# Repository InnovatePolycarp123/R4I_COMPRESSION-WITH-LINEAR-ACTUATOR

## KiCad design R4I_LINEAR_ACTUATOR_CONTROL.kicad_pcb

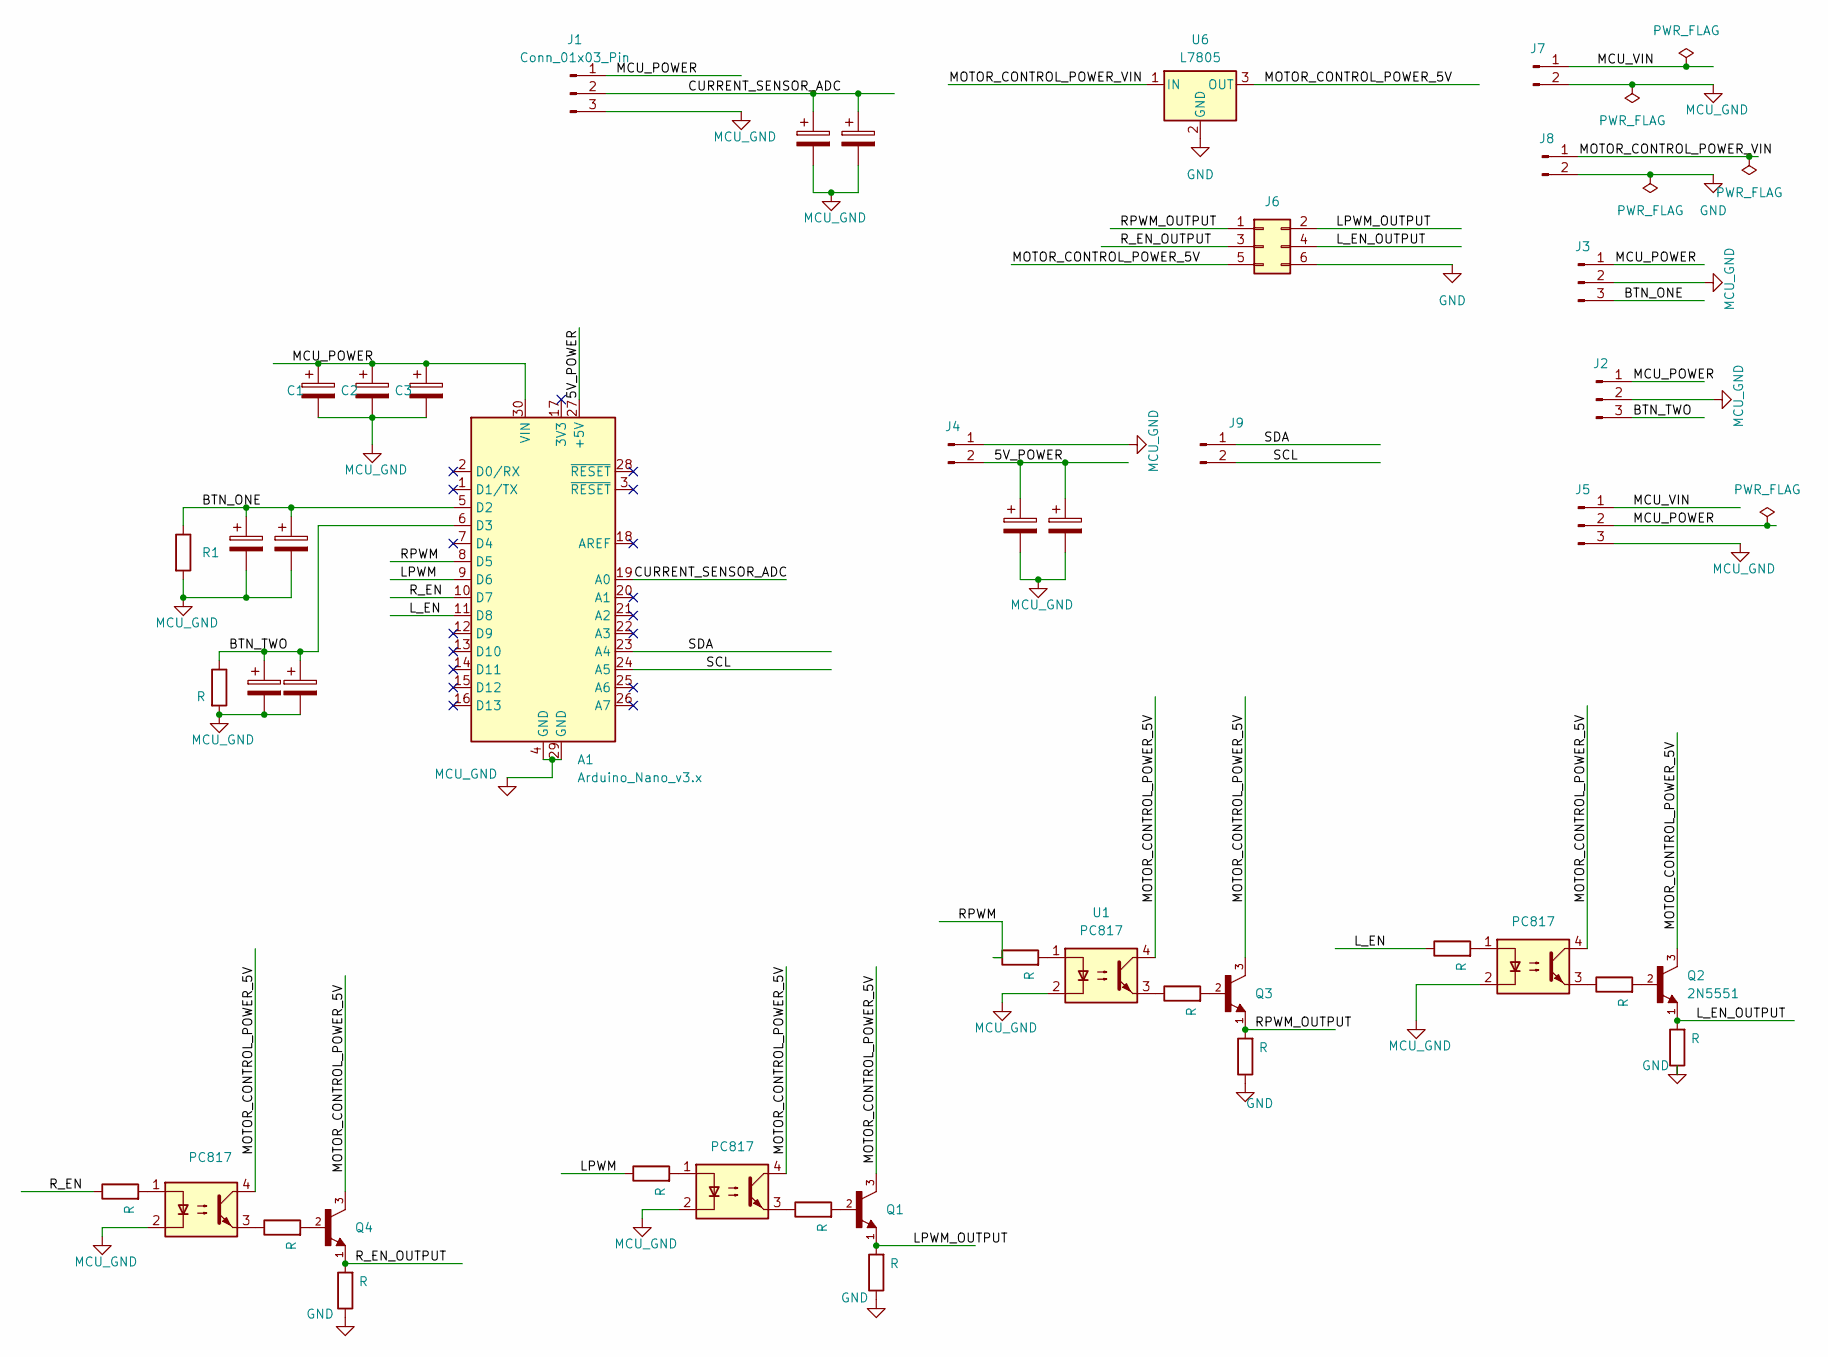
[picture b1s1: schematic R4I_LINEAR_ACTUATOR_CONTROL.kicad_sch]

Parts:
A1: Arduino_Nano_v3.x; Arduino_Nano
C1, C2, C3, C4, C5, C6, C7, C8, C9, C10, C11: C_Polarized; CP_Radial_D5.0mm_P2.50mm
J1, J2, J3, J5: Conn_01x03_Pin; JST_EH_B3B-EH-A_1x03_P2.50mm_Vertical
J4, J7, J8, J9: Conn_01x02_Pin; JST_EH_B2B-EH-A_1x02_P2.50mm_Vertical
J6: Conn_02x03_Row_Letter_Last; PinHeader_2x03_P2.54mm_Vertical
Q1, Q2, Q3, Q4: 2N5551; TO-92L_Wide; PARTREV 5
R1, R2, R3, R4, R5, R6, R7, R8, R9, R10, R11, R12, R13, R14: R; R_Axial_DIN0207_L6.3mm_D2.5mm_P7.62mm_Horizontal
U1, U2, U3, U4: PC817; DIP-4_W7.62mm
U6: L7805; TO-220-3_Vertical

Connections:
/5V_POWER: A1.27 (+5V), C10.1, C11.1, J4.2
/BTN_ONE: A1.5 (D2), C4.1, C5.1, J3.3, R1.1
/BTN_TWO: A1.6 (D3), C6.1, C7.1, J2.3, R2.1
/CURRENT_SENSOR_ADC: A1.19 (A0), C8.1, C9.1, J1.2
/LPWM: A1.9 (D6), R13.1
/LPWM_OUTPUT: J6.2 (Pin_1b), Q1.1, R9.2
/L_EN: A1.11 (D8), R11.1
/L_EN_OUTPUT: J6.4 (Pin_2b), Q2.1, R7.2
/MCU_POWER: A1.30 (VIN), C1.1, C2.1, C3.1, J1.1, J2.1, J3.1, J5.2
/MCU_VIN: J5.1, J7.1
/MOTOR_CONTROL_POWER_5V: J6.5 (Pin_3a), Q1.3, Q2.3, Q3.3, Q4.3, U1.4, U2.4, U3.4, U4.4, U6.3 (OUT)
/MOTOR_CONTROL_POWER_VIN: J8.1, U6.1 (IN)
/RPWM: A1.8 (D5), R14.1
/RPWM_OUTPUT: J6.1 (Pin_1a), Q3.1, R10.2
/R_EN: A1.10 (D7), R12.1
/R_EN_OUTPUT: J6.3 (Pin_2a), Q4.1, R8.2
/SCL: A1.24 (A5), J9.2
/SDA: A1.23 (A4), J9.1
GND: J6.6 (Pin_3b), J8.2, R7.1, R8.1, R9.1, R10.1, U6.2 (GND)
MCU_GND: A1.4 (GND), A1.29 (GND), C1.2, C2.2, C3.2, C4.2, C5.2, C6.2, C7.2, C8.2, C9.2, C10.2, C11.2, J1.3, J2.2, J3.2, J4.1, J5.3, J7.2, R1.2, R2.2, U1.2, U2.2, U3.2, U4.2
unnamed: Q1.2, R3.2
unnamed: Q2.2, R6.2
unnamed: Q3.2, R4.2
unnamed: Q4.2, R5.2
unnamed: R3.1, U2.3
unnamed: R4.1, U1.3
unnamed: R5.1, U3.3
unnamed: R6.1, U4.3
unnamed: R11.2, U4.1
unnamed: R12.2, U3.1
unnamed: R13.2, U2.1
unnamed: R14.2, U1.1

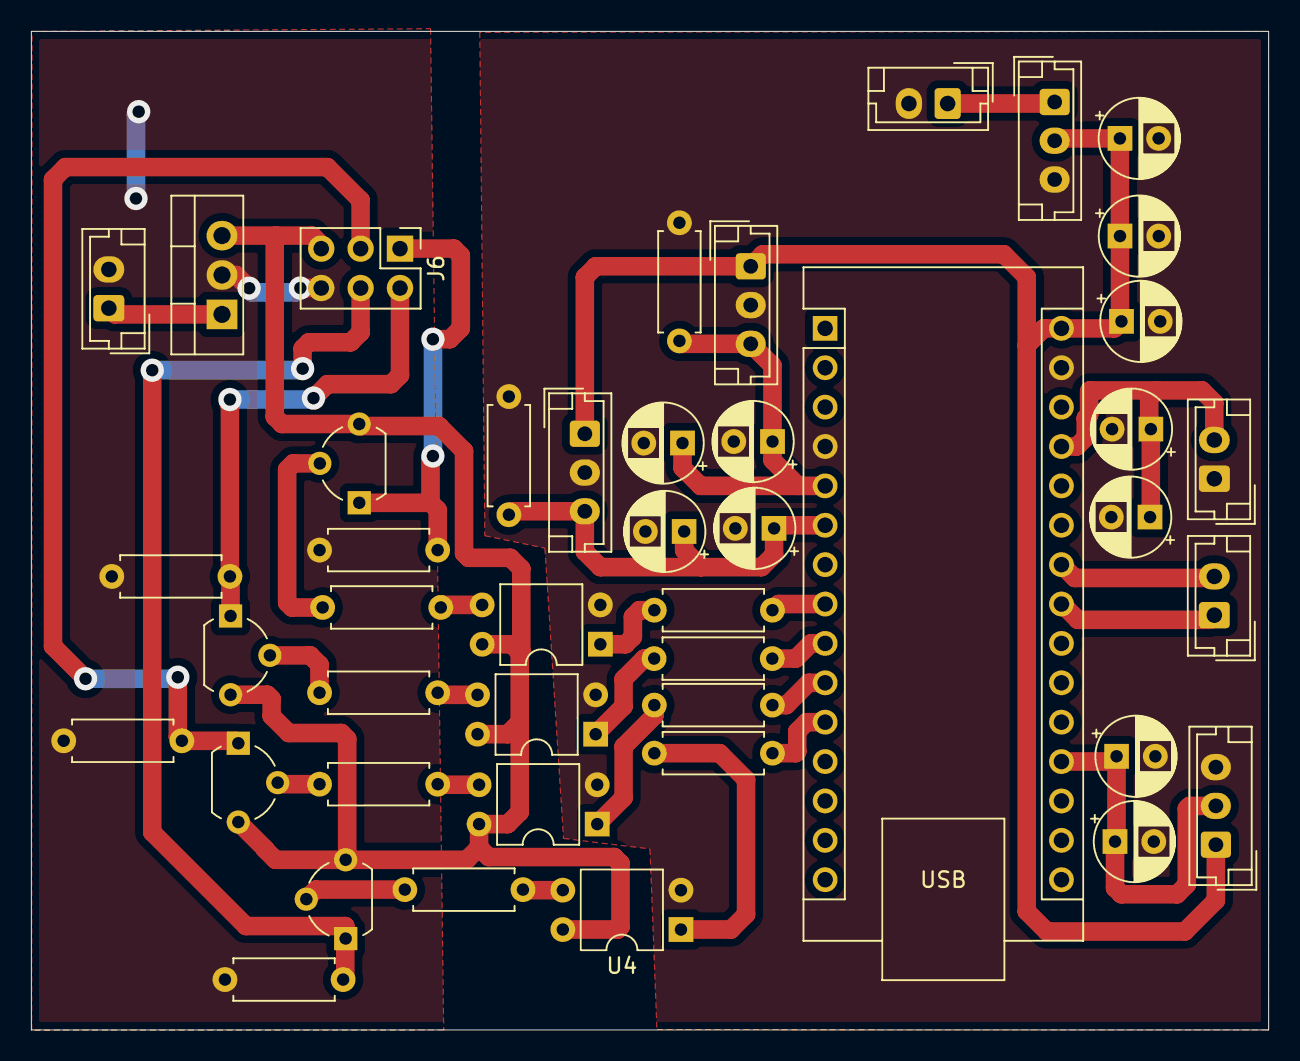
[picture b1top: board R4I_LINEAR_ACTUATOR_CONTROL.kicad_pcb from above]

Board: 2 copper layers, 79.8 x 64.4 mm, 44 parts (0 on the bottom side), 32 nets.

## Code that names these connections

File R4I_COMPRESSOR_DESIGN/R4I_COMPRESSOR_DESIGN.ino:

//Library version:1.1
#include <Wire.h> 
#include <LiquidCrystal_I2C.h>

volatile bool btn_one_state = false;
volatile bool btn_two_state = false;
bool clockwise_button = false;
bool anti_clockwise_button = false;
unsigned long previous_millis_clockwise = 0;
unsigned long previous_millis_anti_clockwise = 0;
unsigned long previous_millis_direction_control= 0;
unsigned long previous_millis_current_monitor = 0;
int debounce_interval = 10;

const float sensorOffset = 2.5;      // Offset voltage at 0A (in volts, typical for ACS712)
const float sensitivity = 0.066;    // Sensitivity in V/A for ACS712 30A version
const float referenceVoltage = 4.55 ; // Reference voltage for the ADC
const int adcResolution = 1023;     // 10-bit ADC
const int numSamples = 100;         // Number of samples for averaging




int count = 0;

#define btn_one 2
#define btn_two 3
#define CURRENT_SENSE A0
#define RPWM 5
#define LPWM 6
#define R_EN  7
#define L_EN  8

LiquidCrystal_I2C lcd(0x27,20,4);  // set the LCD address to 0x27 for a 16 chars and 2 line display


void button_control();
void motor_setup();
void motor_disable();
void  motor_enable();
void direction_control(float current_reading, int refresh_rate = 50);
float current_monitor( int refresh_rate = 100);

void button_one(){

  unsigned long current_millis = millis();
 if((current_millis -  previous_millis_clockwise) > debounce_interval){
   previous_millis_clockwise = current_millis;
   if (digitalRead(btn_one)){
      btn_one_state = true;

   }else{

     btn_one_state = false;
  }


  }

}


void button_two(){

  unsigned long current_millis = millis();
  if ( (current_millis -  previous_millis_anti_clockwise) > debounce_interval) {
    previous_millis_anti_clockwise = current_millis;

     if (digitalRead(btn_two)){
       btn_two_state = true;

    }else{
     btn_two_state = false;
    }

  
  } 

}

void setup() {
   Serial.begin(9600);

  pinMode(CURRENT_SENSE, INPUT);
  pinMode(btn_one, INPUT);
  pinMode(btn_two, INPUT);
  
  motor_setup();
  motor_enable();

 
  attachInterrupt(digitalPinToInterrupt(btn_one), button_one, CHANGE);
  attachInterrupt(digitalPinToInterrupt( btn_two), button_two, CHANGE);

  lcd.init();                      // initialize the lcd 
  // Print a message to the LCD.
  lcd.backlight();
  lcd.blink();
  lcd.setCursor(4,1);
  lcd.print("S-COMPACTIFY");
  lcd.setCursor(0,3);
  lcd.print("Powered By Innov8Hub");
}



void loop(){

  float current_reading = current_monitor();
  Serial.print("Current_reading: ");
  Serial.println(current_reading);
 
  
   direction_control( current_reading);

  
 

   button_control();
 


}
  

void motor_setup(){
  
 pinMode(RPWM, OUTPUT);   
 pinMode(LPWM, OUTPUT); 
 pinMode( R_EN, OUTPUT);   
 pinMode(L_EN , OUTPUT);
 pinMode(btn_one, INPUT);
pinMode(btn_two, INPUT);

}

void motor_disable(){
  
digitalWrite(R_EN, LOW) ;
digitalWrite(L_EN, LOW) ;

}


void motor_enable(){
  
digitalWrite(R_EN, HIGH) ;
digitalWrite(L_EN, HIGH) ;

}

void direction_control(float current_reading, int refresh_rate = 50){

 unsigned long current_millis = millis();
  if ((current_millis - previous_millis_direction_control) >  refresh_rate){

    if (clockwise_button) {
    clockwise_button = false;
    motor_enable();
    lcd.clear();
    lcd.setCursor(0,0);
    lcd.print("Button one pressed");
    lcd.setCursor(0,3);
    lcd.print("Current: ");
    lcd.print(String(current_reading));
    analogWrite(LPWM, 255);
    analogWrite(RPWM, 0);


    delay(20);
    
    } else if (anti_clockwise_button) {

   
    anti_clockwise_button = false;
    
    motor_enable();
    lcd.clear();
    lcd.setCursor(0,0);
    lcd.print("Button two pressed");
    lcd.setCursor(0,3);
    lcd.print("Current: ");
    lcd.print(String(current_reading));
    analogWrite(LPWM, 0);
    analogWrite(RPWM, 255);
    delay(20);

    } else {
     motor_disable();
      lcd.clear();
      lcd.setCursor(0,0);
      lcd.print("No button pressed");
      lcd.setCursor(0,3);
      lcd.print("Current: ");
      lcd.print(String(current_reading, 1));
     analogWrite(LPWM, 0);
     analogWrite(RPWM, 0); 
   }
 }

}

void button_control(){

 if(btn_one_state ){
  clockwise_button = true;

 } else if (btn_two_state){
  anti_clockwise_button = true;
 }
  
}


float current_monitor(int refresh_rate = 100 ){ // this is a cumbersome way of doing this. I could easily remove the array. However, I'm testing my knowledge of C. 
  unsigned long current_millis = millis();
   
  if ((current_millis - previous_millis_current_monitor) > refresh_rate){

    previous_millis_current_monitor = current_millis;

    long adcSum = 0;

  for (int i = 0; i < numSamples; i++) {
    adcSum += analogRead( CURRENT_SENSE);
    delay(1); // Small delay to reduce noise
  }
  float adcAverage = adcSum / float(numSamples);

  // Convert ADC value to voltage
  float voltage = (adcAverage * referenceVoltage) / adcResolution;

  // Calculate current
  float current = (voltage - sensorOffset) / sensitivity;
  

   return    current + 0.6;

  }
  
}

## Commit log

2024-12-13 This repository is for an R4I project that uses aa linear actuator to compress stuuf
    it has two code: one uses a current sensor for limmiting the linear actuator, but the calibration took time. So, we went for using count instead.
